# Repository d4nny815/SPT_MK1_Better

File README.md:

# SPT_MK1_Better
- **Goal**: get MK1 running again as quick as possible with bare minimum requirements

## How to setup MK1

# **For Test Stand still using the TEENSY**

### Test Stand
- If anything goes wrong, I can't help you. all the software in the repo is for the ESP32 now, you'd have to go back to an older commit
- Plug in the power supply
- Connect the DB9 cable to the test stand
- Connect the ESTOP wires to the test stand
- Connect the power supply to the test stand
- Go connect the control Box to the computer
- If you have to connect to the teensy make sure that 24V **IS NOT** connect to the 5V buck converter, This can fry the board.
- Then connect the usb cable to the teensy for debugging

### Control Box
**NOTE: data accuracy over Serial for the teensy rev is spotty, I don't think its accurate. It's fixed with the esp rev. But the controls with all still work**
- connect the DB9 cable
- connect ESTOP cable to VCC and GND
- connect control box esp32 to computer
- go to `data_collection/`
- open `mk1_better_v1_monitor.ctl` in CoolTerm
- configure COM port of esp32 in CoolTerm
- configure baud rate to 115200
- click connect in CoolTerm
- on top toolbar, click `View Chart` under the `View` dropdown
- under the `Connection` -> `Capture to Text/Binary File` -> `Start Capture`
- name the file <month.day.year>_<typeOfRun>_run<Number>.txt (ex. 11.19.23_hotfire_run1.txt)
- pause the recording `Capture to Text/Binary File` -> `Pause Capture` or Ctrl+Alt+R **at the beginning** so the file doesn't get too big 
- right before you start the run on the test stand, click `Capture to Text/Binary File` -> `Start Capture` or Ctrl+R to start recording
- after the run, click `Capture to Text/Binary File` -> `Stop Capture` or Ctrl+Shift+R to stop recording
- run `format_to_csv.py` format the file to csv and clean up the time
- open the csv file in excel and save as .xlsx if you're boring
- if youre a CHAD open `mk1_better_v1.m` in matlab
- change the file name to the file you just recorded
- run the script
- Oooooooh pretty graphs

### This is for the new esp32 boards [**DO NOT USE**]

# Test Stand
- Plug in the power supply
- Connect the power supply to the test stand
- Connect the ESTOP wires to the test stand
- Go connect the control Box to the computer

# Control Box
- if anything goes wrong, deal with it
- download and install CoolTerm https://freeware.the-meiers.org/
- if you are on windows, you will need to install the driver for the CP2102 chip https://www.silabs.com/developers/usb-to-uart-bridge-vcp-drivers?tab=downloads
- Go to `data_collection/`
- connect control box esp32 to computer
- open mk1_better_v2_monitor.ctl in CoolTerm
- configure COM port of esp32 in CoolTerm
- configure baud rate to 230400 
- click connect in CoolTerm
- on top toolbar, click `View Chart` under the `View` dropdown
- under the `connection` dropdown, click `Capture to Text/Binary File` -> `Start Capture`
- name the file <month.day.year>_<typeOfRun>_run<Number>.txt
- pause the recording `Capture to Text/Binary File` -> `Pause Capture` or Ctrl+Alt+R so the file doesn't get too big 
- right before you start the run, click `Capture to Text/Binary File` -> `Start Capture` or Ctrl+R to start recording
- after the run, click `Capture to Text/Binary File` -> `Stop Capture` or Ctrl+Shift+R to stop recording
- run `format_to_csv.py` format the file to csv and clean up the time
- open the csv file in excel and save as .xlsx if you're boring
- if youre a CHAD open `mk1_better_v2.m` in matlab
- change the file name to the file you just recorded
- run the script
- Oooooooh pretty graphs

## How project is organized
- `master_test_stand` code for test stand 
- `slave_control_box` code for  control box
- `data_collection/` is for Serial monitoring
- `ltspice` test circuits in LTSPICE

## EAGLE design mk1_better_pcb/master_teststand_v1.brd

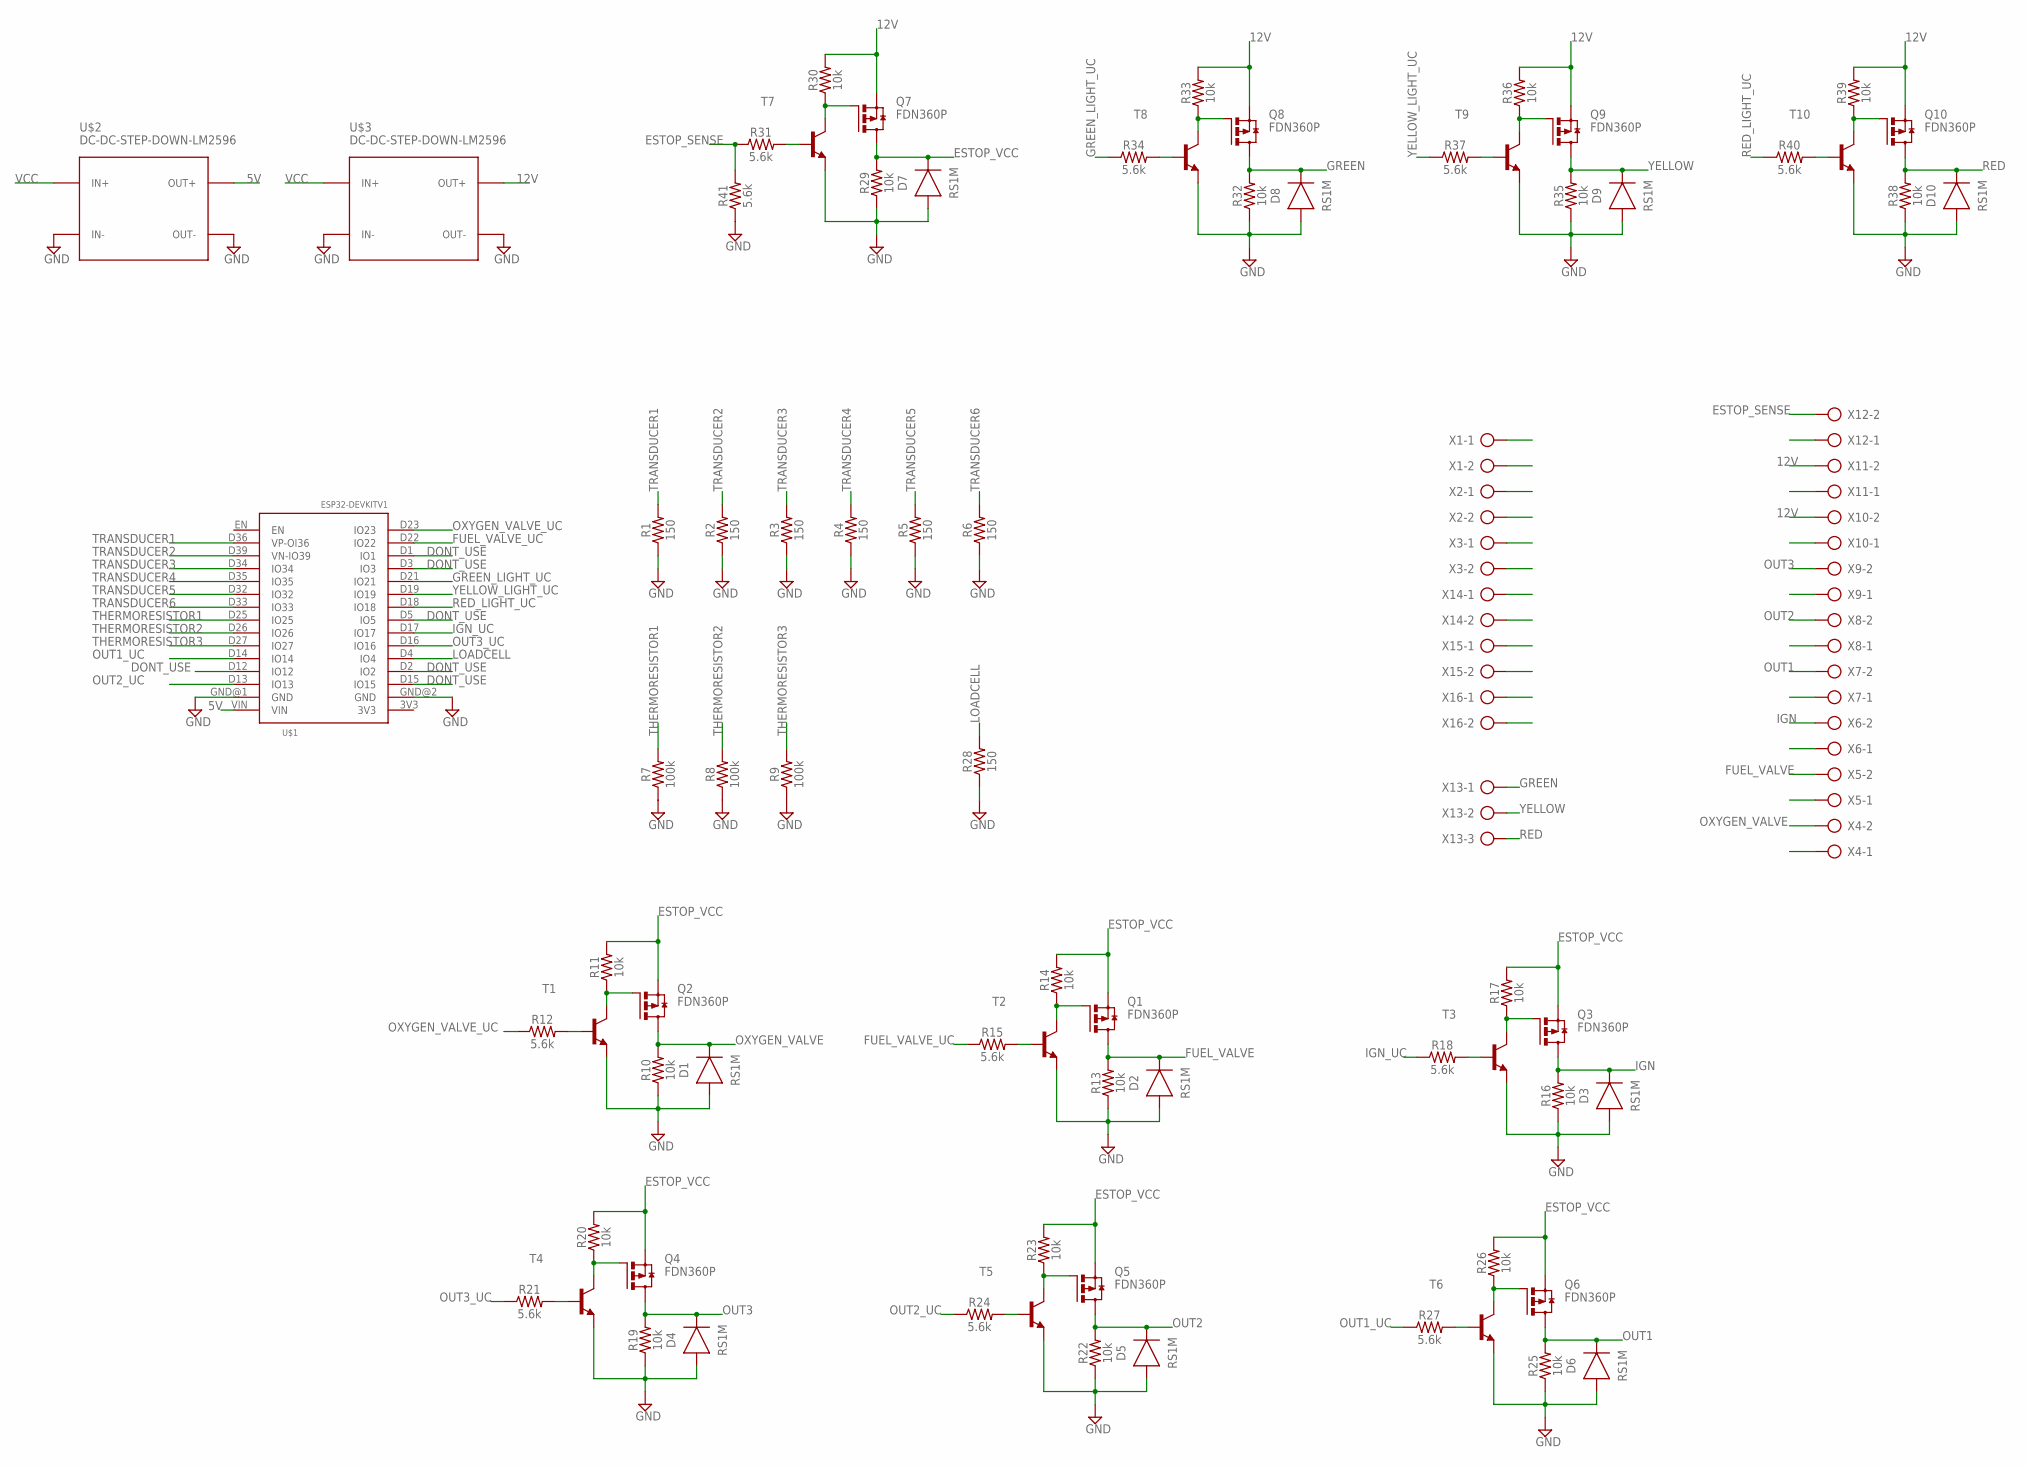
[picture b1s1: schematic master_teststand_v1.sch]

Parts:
D1, D2, D3, D4, D5, D6, D7, D8, D9, D10: RS1M; DIOM5226X290N
Q1, Q2, Q3, Q4, Q5, Q6, Q7, Q8, Q9, Q10: FDN360P; SUPER-SOT3
R1, R2, R3, R4, R5, R6, R28: 150; 0603
R7, R8, R9: 100k; 0603
R10, R11, R13, R14, R16, R17, R19, R20, R22, R23, R25, R26, R29, R30, R32, R33, R35, R36, R38, R39: 10k; 0603
R12, R15, R18, R21, R24, R27, R31, R34, R37, R40, R41: 5.6k; 0603
T1, T2, T3, T4, T5, T6, T7, T8, T9, T10: MMBT2222ALT1-NPN-SOT23-BEC; SOT23-BEC
U$1: ESP32DEVKITV1; ESP32-DEVKITV1
U$2, U$3: DC-DC-STEP-DOWN-LM2596
X1, X2, X3, X4, X5, X6, X7, X8, X9, X10, X11, X12, X14, X15, X16: AK300/2
X13: AK300/3

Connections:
5V: U$1.VIN, U$2.OUT+
12V: Q7.2 (S), Q8.2 (S), Q9.2 (S), Q10.2 (S), R30.2, R33.2, R36.2, R39.2, U$3.OUT+, X10.2, X11.2
DONT_USE: U$1.D1 (IO1), U$1.D2 (IO2), U$1.D3 (IO3), U$1.D5 (IO5), U$1.D12 (IO12), U$1.D15 (IO15)
ESTOP_SENSE: R31.1, R41.2, X12.2
ESTOP_SENSE1: X1.2
ESTOP_SENSE2: X2.2
ESTOP_SENSE3: X3.2
ESTOP_SENSE4: X14.2
ESTOP_SENSE5: X15.2
ESTOP_SENSE6: X16.2
ESTOP_VCC: D7.1 (C), Q1.2 (S), Q2.2 (S), Q3.2 (S), Q4.2 (S), Q5.2 (S), Q6.2 (S), Q7.3 (D), R11.2, R14.2, R17.2, R20.2, R23.2, R26.2, R29.2
FUEL_VALVE: D2.1 (C), Q1.3 (D), R13.2, X5.2
FUEL_VALVE_UC: R15.1, U$1.D22 (IO22)
GND: D1.2 (A), D2.2 (A), D3.2 (A), D4.2 (A), D5.2 (A), D6.2 (A), D7.2 (A), D8.2 (A), D9.2 (A), D10.2 (A), R1.1, R2.1, R3.1, R4.1, R5.1, R6.1, R7.1, R8.1, R9.1, R10.1, R13.1, R16.1, R19.1, R22.1, R25.1, R28.1, R29.1, R32.1, R35.1, R38.1, R41.1, T1.E, T2.E, T3.E, T4.E, T5.E, T6.E, T7.E, T8.E, T9.E, T10.E, U$1.GND@1 (GND), U$1.GND@2 (GND), U$2.IN-, U$2.OUT-, U$3.IN-, U$3.OUT-
GREEN: D8.1 (C), Q8.3 (D), R32.2, X13.1
GREEN_LIGHT_UC: R34.1, U$1.D21 (IO21)
IGN: D3.1 (C), Q3.3 (D), R16.2, X6.2
IGN_UC: R18.1, U$1.D17 (IO17)
LOADCELL: R28.2, U$1.D4 (IO4)
unnamed: Q1.1 (G), R14.1, T2.C
unnamed: R15.2, T2.B
unnamed: Q2.1 (G), R11.1, T1.C
unnamed: Q3.1 (G), R17.1, T3.C
unnamed: R12.2, T1.B
unnamed: R18.2, T3.B
unnamed: Q4.1 (G), R20.1, T4.C
unnamed: R21.2, T4.B
unnamed: Q5.1 (G), R23.1, T5.C
unnamed: R24.2, T5.B
unnamed: Q6.1 (G), R26.1, T6.C
unnamed: R27.2, T6.B
unnamed: Q7.1 (G), R30.1, T7.C
unnamed: R31.2, T7.B
unnamed: Q8.1 (G), R33.1, T8.C
unnamed: R34.2, T8.B
unnamed: Q9.1 (G), R36.1, T9.C
unnamed: R37.2, T9.B
unnamed: Q10.1 (G), R39.1, T10.C
unnamed: R40.2, T10.B
OUT1: D6.1 (C), Q6.3 (D), R25.2, X7.2
OUT1_UC: R27.1, U$1.D14 (IO14)
OUT2: D5.1 (C), Q5.3 (D), R22.2, X8.1, X8.2
OUT2_UC: R24.1, U$1.D13 (IO13)
OUT3: D4.1 (C), Q4.3 (D), R19.2, X9.2
OUT3_UC: R21.1, U$1.D16 (IO16)
OXYGEN_VALVE: D1.1 (C), Q2.3 (D), R10.2, X4.2
OXYGEN_VALVE_UC: R12.1, U$1.D23 (IO23)
RED: D10.1 (C), Q10.3 (D), R38.2, X13.3
RED_LIGHT_UC: R40.1, U$1.D18 (IO18)
THERMORESISTOR1: R7.2, U$1.D25 (IO25)
THERMORESISTOR2: R8.2, U$1.D26 (IO26)
THERMORESISTOR3: R9.2, U$1.D27 (IO27)
TRANSDUCER1: R1.2, U$1.D36 (VP-OI36)
TRANSDUCER2: R2.2, U$1.D39 (VN-IO39)
TRANSDUCER3: R3.2, U$1.D34 (IO34)
TRANSDUCER4: R4.2, U$1.D35 (IO35)
TRANSDUCER5: R5.2, U$1.D32 (IO32)
TRANSDUCER6: R6.2, U$1.D33 (IO33)
VCC: U$2.IN+, U$3.IN+
YELLOW: D9.1 (C), Q9.3 (D), R35.2, X13.2
YELLOW_LIGHT_UC: R37.1, U$1.D19 (IO19)

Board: 2 copper layers, 90 parts (0 on the bottom side), 55 nets, no tracks yet.

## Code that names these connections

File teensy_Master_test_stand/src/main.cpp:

#include <Arduino.h>
#include <stdlib.h>
#include <avr/io.h>
#include "DigitalInput.h"
#include "DigitalOutput.h"
#include "SolenoidValve.h"
#include "Transducer.h"
#include "LoadCell.h"
#include "DataLogger.h"


// INPUT PINS
#define BAUD_RATE 9600  // BAUDRATE for teensy communications
// Analog IN
#define TRANSDUCER1_PIN 18
#define TRANSDUCER2_PIN 17
#define TRANSDUCER3_PIN 16
#define LOADCELL_PIN 19
// Digital IN
#define ESTOP_PIN 32

// OUTPUT PINS
#define STOPLIGHT_GREEN_PIN 2
#define STOPLIGHT_YELLOW_PIN 3
#define STOPLIGHT_RED_PIN 4
#define OXYGEN_VALVE_PIN 7
#define FUEL_VALUE_PIN 8
#define IGN_PIN 9
#define out1_pin 30
#define out2_pin 31

// Define the states of the system
enum State {
  POWER_ON,
  KSI,
  LAUNCH,
  FAIL, 
  TEST
};
State STATE;
bool first_time_in_state = true;

// Instantiate every component in the system
SerialData serial_data;
DigitalOutput red_light(STOPLIGHT_RED_PIN);  // lights are active low
DigitalOutput yellow_light(STOPLIGHT_YELLOW_PIN);  // lights are active low
DigitalOutput green_light(STOPLIGHT_GREEN_PIN);  // lights are active low
DigitalOutput ign_wire(IGN_PIN);
DigitalOutput out1(out1_pin);
DigitalOutput out2(out2_pin);
SoleinoidValve oxygen_valve(OXYGEN_VALVE_PIN, 100, 90);
SoleinoidValve fuel_valve(FUEL_VALUE_PIN, 100, 90);
Loadcell loadcell(LOADCELL_PIN, 50);
DigitalInput estop(ESTOP_PIN);
Transducer ducer1(TRANSDUCER1_PIN);
Transducer ducer2(TRANSDUCER2_PIN);
Transducer ducer3(TRANSDUCER3_PIN);
Transducer ducer_arr[] = {ducer1, ducer2, ducer3};


// b7 | b6 | b5 | b4 | b3 | b2 | b1 | b0
// heartbeat | valid | sw_ign | sw_launch | sw_oxygen | sw_fuel | launch_btn | ksi 
int comms_status;
uint8_t comms = 0x00;
const u_int8_t bit_ksi = 1 << 0;
const u_int8_t bit_launch_btn = 1 << 1;
const u_int8_t bit_sw_fuel = 1 << 2;
const u_int8_t bit_sw_oxygen = 1 << 3;
const u_int8_t bit_sw_launch = 1 << 4;
const u_int8_t bit_sw_ign = 1 << 5;
const u_int8_t bit_valid = 1 << 6;
u_int8_t bit_heartbeat = 1 << 7;

void setup() {
	Serial.begin(115200);
	Serial1.begin(BAUD_RATE);
	serial_data.set_start_time();
	STATE = POWER_ON; 

	// STATE = TEST;
}

/************************************************
 * HERE STARTS THE REAL CODE
 *  /\/\/\                            /  \
 * | \  / |                         /      \
 * |  \/  |                       /          \
 * |  /\  |----------------------|     /\     |
 * | /  \ |                      |    /  \    |
 * |/    \|                      |   /    \   |
 * |\    /|                      |  | (  ) |  |
 * | \  / |                      |  | (  ) |  |
 * |  \/  |                 /\   |  |      |  |   /\
 * |  /\  |                /  \  |  |      |  |  /  \
 * | /  \ |               |----| |  |      |  | |----|
 * |/    \|---------------|    | | /|   .  |\ | |    |
 * |\    /|               |    | /  |   .  |  \ |    |
 * | \  / |               |    /    |   .  |    \    |
 * |  \/  |               |  /      |   .  |      \  |
 * |  /\  |---------------|/        |   .  |        \|
 * | /  \ |              /   NASA   |   .  |  NASA    \
 * |/    \|              (          |      |           )
 * |/\/\/\|               |    | |--|      |--| |    |
 * ------------------------/  \-----/  \/  \-----/  \--------
 *                         \\//     \\//\\//     \\//
 *                          \/       \/  \/       \/
 ************************************************
*/

void power_on_state () {
	if (first_time_in_state) {
		// Serial.println("POWERON state entry");
		ign_wire.turn_off();
		oxygen_valve.turn_off();
		fuel_valve.turn_off();
		green_light.turn_off();
		yellow_light.turn_on();
		red_light.turn_on();
		first_time_in_state = false;
	}
	return;
};


void ksi_state () {
	if (first_time_in_state) {
		// Serial.println("KSI state entry");
		ign_wire.turn_off();
		oxygen_valve.turn_off();
		fuel_valve.turn_off();
		green_light.turn_on();
		yellow_light.turn_off();
		red_light.turn_on();
		first_time_in_state = false;
	}

	if ((comms & bit_sw_fuel) && (comms & bit_sw_oxygen)) {
		oxygen_valve.turn_off();
		fuel_valve.turn_off();
	}
	else if ((comms & bit_sw_fuel) && !(comms & bit_sw_oxygen)) {
		fuel_valve.turn_on();
		oxygen_valve.turn_off();
	}
	else if ((comms & bit_sw_oxygen) && !(comms & bit_sw_fuel)) {
		oxygen_valve.turn_on();
		fuel_valve.turn_off();
	} 
	else {
		oxygen_valve.turn_off();
		fuel_valve.turn_off();
	}
	return;
};

void launch_state () {
	if (first_time_in_state) {
		// Serial.println("LAUNCH state entry");
		ign_wire.turn_off();
		oxygen_valve.turn_off();
		fuel_valve.turn_off();
		green_light.turn_on();
		yellow_light.turn_on();
		red_light.turn_off();
		first_time_in_state = false;
	}
	
	if ((comms & bit_sw_launch)) {
		oxygen_valve.turn_on();
		// * comment this to remove it
		delay(100); // shitty blocking delay but it'll do 
		fuel_valve.turn_on();
	}
	else {
		oxygen_valve.turn_off();
		fuel_valve.turn_off();
	}

	if ((comms & bit_sw_ign)) ign_wire.turn_on();	
	else ign_wire.turn_off();

	return;
};

void fail_state () {
	green_light.turn_off();
	yellow_light.turn_off();
	red_light.turn_off();

	// Serial.println("FAIL");

	ign_wire.turn_off();
	oxygen_valve.turn_off();
	fuel_valve.turn_off();
	return;
};

void test_state() {
	return;
}

void loop() {
	if (!(digitalRead(ESTOP_PIN))) {
		STATE = FAIL;
	}

	if (Serial1.available()) {
		comms_status = Serial1.readBytes(&comms, 1);
		
		if (comms == -1) { STATE = FAIL; } // failed reading serial transmission
		if (!(comms & bit_valid)) { STATE = FAIL; } // valid bit wasn't sent through
		// Serial.print("from comms: ");
		// Serial.println(comms, BIN);
	}

	// if (Serial.available()) {
	// 	comms_status = Serial.readBytes(&comms, 1);
	// 	if (comms == -1) { STATE = FAIL; } // failed reading serial transmission
	// 	if (!(comms & bit_valid)) { STATE = FAIL; } // valid bit wasn't sent through
	// 	Serial.print("from comms: ");
	// 	Serial.println(comms, BIN);
	// }

	serial_data.accummulate_data(ducer_arr, loadcell);
	serial_data.send_serial_data();
	// serial_data.print_serial_data();

	switch (STATE) {
		case (POWER_ON): 
			power_on_state();

			if (comms & bit_ksi) {
				STATE = KSI;
				first_time_in_state = true;
			}
			break;

		case (KSI): 
			ksi_state();

			if (comms & bit_launch_btn) {
				STATE = LAUNCH;
				first_time_in_state = true;
			}
			if (!(comms & bit_ksi)) {
				STATE = POWER_ON;
				first_time_in_state = true;
			}
			break;

		case (LAUNCH): 
			launch_state();

			if (!(comms & bit_ksi)) {
				STATE = POWER_ON;
				first_time_in_state = true;
			}
			break;

		case (FAIL): 
			fail_state();

			if (comms == 0xC0 && digitalRead(ESTOP_PIN)) {
				STATE = POWER_ON;
				first_time_in_state = true;
				green_light.turn_off();
				yellow_light.turn_off();
				red_light.turn_off();
			}
			break;

		case (TEST):
			test_state();
			break;
		default:
			STATE = FAIL;
	}
}

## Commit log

2023-10-21 platformIO
2023-10-22 simple start
2023-10-23 basic setup
2023-10-25 Added ducer lib
2023-10-25 test push
2023-10-26 clean setup
2023-10-26 done with pc
2023-10-27 Added the ducer file and added a conversion of voltage to psi
2023-10-27 updated ltspice
2023-10-28 data loggin
2023-10-28 Added the first two stages
2023-10-28 transducer
2023-10-28 working
2023-10-28 wrong branch
2023-10-28 ready for bench
2023-10-28 data logger 75%
2023-10-29 firmware almost done
2023-10-29 breadboard confirmed
2023-10-30 made output faster
2023-11-06 restructure
2023-11-06 added serial comms, idk if working
2023-11-06 small scale comms
2023-11-07 Slave box switch bit conversion
2023-11-07 test stand comms
2023-11-08 working without loadcell and ducer confirmation
2023-11-08 working but not good
2023-11-09 test
2023-11-14 added improved comms
2023-11-16 updated NOV 15
2023-11-16 working outputs on test stand, need to check data collection
2023-11-17 running hotfire
2023-11-18 run1
2023-11-18 esp_now control box
2023-11-18 esp_now for test stand, also convert to esp MCU
2023-11-22 data collection
2023-11-23 testStand freeRTOS
2023-11-23 control Box
2023-11-23 waiting for PCB
2023-11-26 working on it
2023-11-28 updated docs
2023-11-28 teensy code added
2023-11-28 teensy
2023-11-30 worknight
2023-11-30 estop not working and switches not working
2023-12-01 worked on sensors
2023-12-02 Slave box update
2023-12-02 working on test stand
2023-12-02 final push
2023-12-02 on stadn
2023-12-02 slave box push
2023-12-02 matlab
2023-12-02 removed prev message
2023-12-02 worked on hotfire
2023-12-03 plotter
2023-12-03 python plotter working on windows
2023-12-06 coldflow 12/5
2024-01-27 for testing 1/26/24
2024-01-27 changed data collection format

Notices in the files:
parts and their libraries:
SparkFun-Resistors: Licensing: Creative Commons ShareAlike 4.0 International - https://creativecommons.org/licenses/by-sa/4.0
